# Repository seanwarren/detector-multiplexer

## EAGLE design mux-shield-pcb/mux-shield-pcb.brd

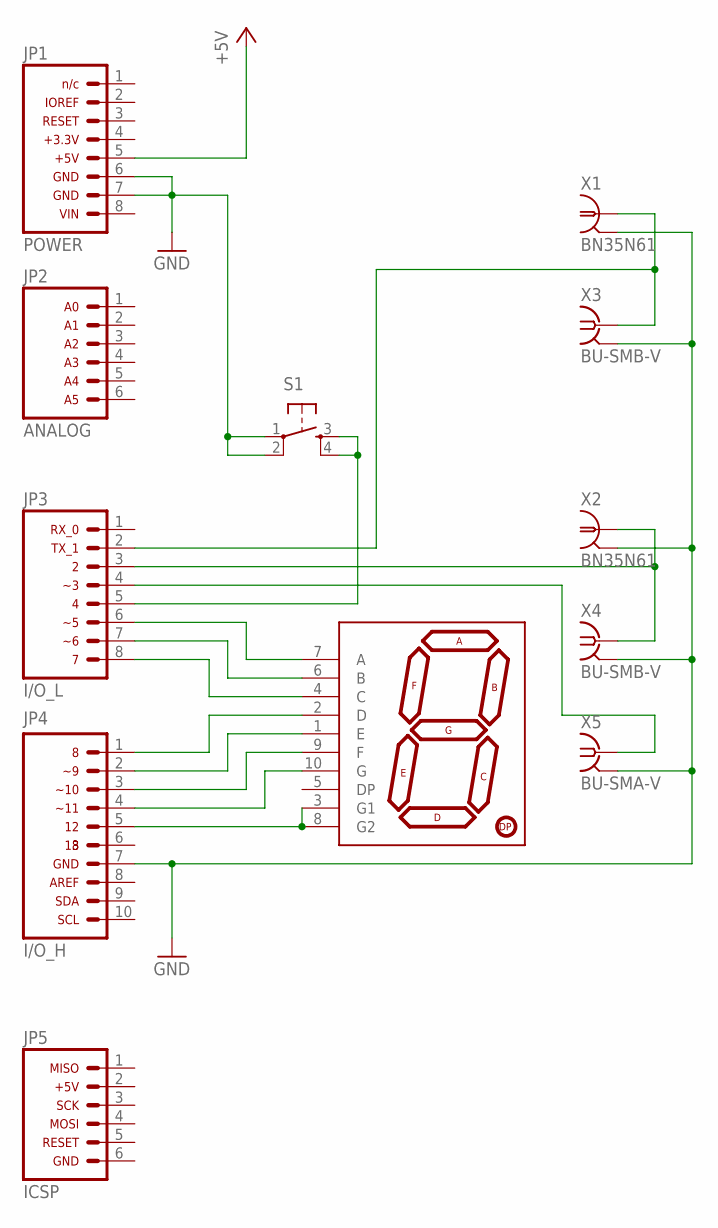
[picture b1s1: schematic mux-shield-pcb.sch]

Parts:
JP1: ARDUINO_CONN-POWERSIP; CONN-1X08
JP2: ARDUINO_CONN-ANALOGSIP; CONN-1X06
JP3: ARDUINO_CONN-IO_LSIP; CONN-1X08
JP4: ARDUINO_CONN-IO_HSIP; CONN-1X10
JP5: ARDUINO_CONN-ICSP; CONN-2X03
S1: TAC_SWITCHPTH; TACTILE-PTH
U$1: 7-SEGMENT-DISPLAY-1"-RED; 7-SEGMENT-1"PTH
X1, X2: BN35N61; B35N61
X3, X4: BU-SMB-V
X5: BU-SMA-V

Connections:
+5V: JP1.5
GND: JP1.6, JP1.7, JP4.7, S1.1, S1.2, X1.2, X1.3 (2), X1.4 (2), X1.5 (2), X2.2, X2.3 (2), X2.4 (2), X2.5 (2), X3.2, X3.3 (2), X3.4 (2), X3.5 (2), X4.2, X4.3 (2), X4.4 (2), X4.5 (2), X5.2, X5.3 (2), X5.4 (2), X5.5 (2)
unnamed: JP3.2, X1.1, X3.1
unnamed: JP3.4, X5.1
unnamed: JP3.3, X2.1, X4.1
unnamed: JP3.5, S1.3, S1.4
unnamed: JP4.5, U$1.3 (G1), U$1.8 (G2)
unnamed: JP3.6, U$1.7 (A)
unnamed: JP3.7, U$1.6 (B)
unnamed: JP3.8, U$1.4 (C)
unnamed: JP4.1, U$1.2 (D)
unnamed: JP4.2, U$1.1 (E)
unnamed: JP4.3, U$1.9 (F)
unnamed: JP4.4, U$1.10 (G)

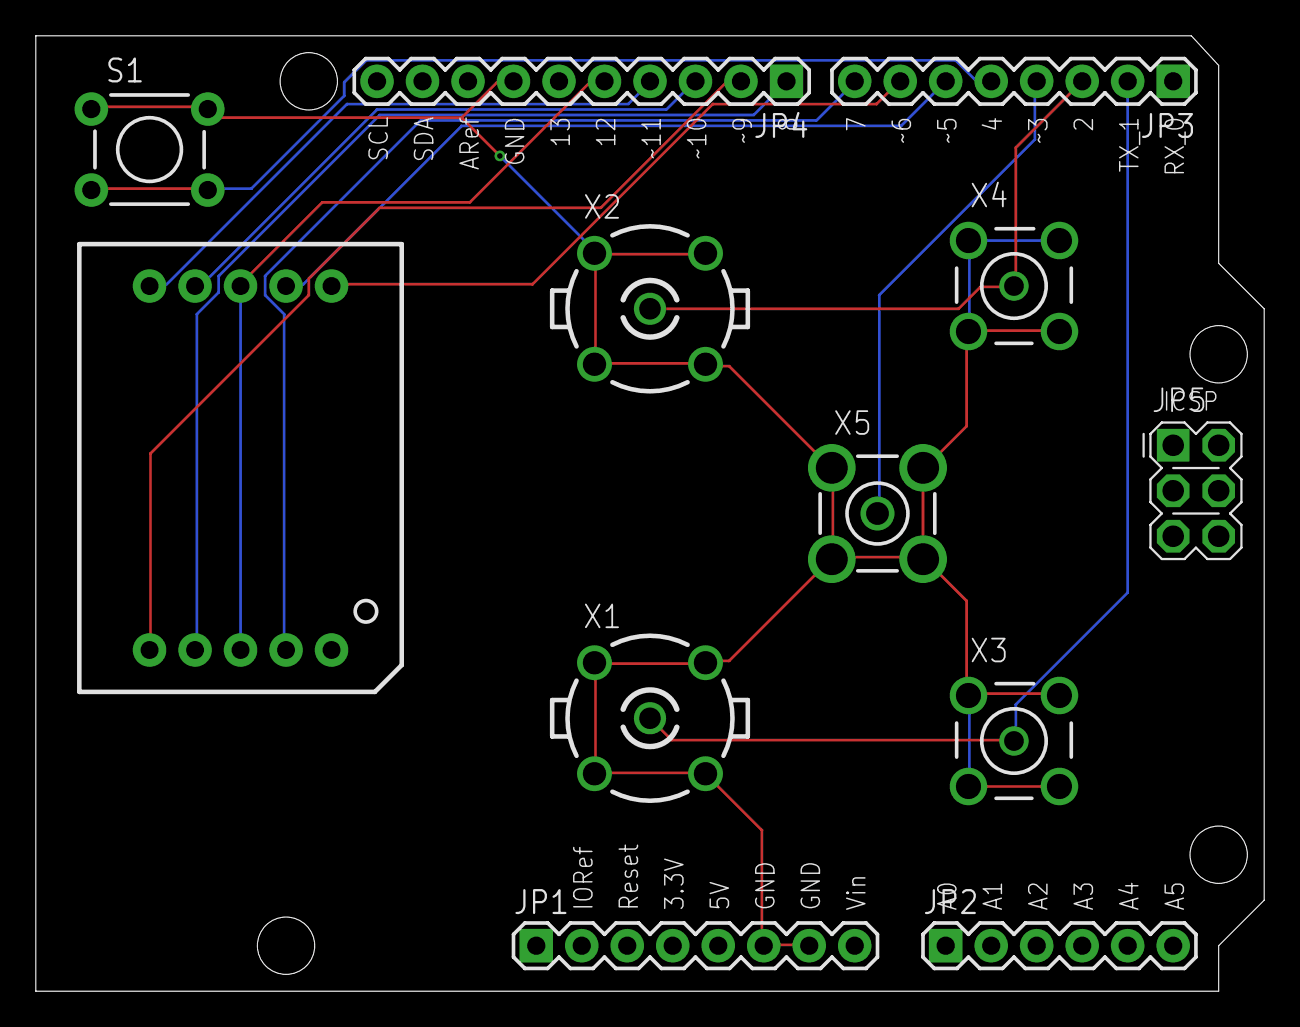
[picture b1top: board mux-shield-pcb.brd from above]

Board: 2 copper layers, 68.6 x 53.3 mm, 12 parts (0 on the bottom side), 13 nets.

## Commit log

2015-06-16 Add PCB layout
2015-07-01 Initial commit of firmware for multiplexing electronics
2015-07-01 Update PCB connecting button to ground rather than 5V
2015-09-24 Add computer control for switch
2015-09-24 Set mux pin to output
2016-03-22 Make sure that detector is switched back to channel 1 on exit

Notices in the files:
parts and their libraries:
SparkFun-Retired: Licensing:Creative Commons ShareAlike 4.0 International - https://creativecommons.org/licenses/by-sa/4.0
